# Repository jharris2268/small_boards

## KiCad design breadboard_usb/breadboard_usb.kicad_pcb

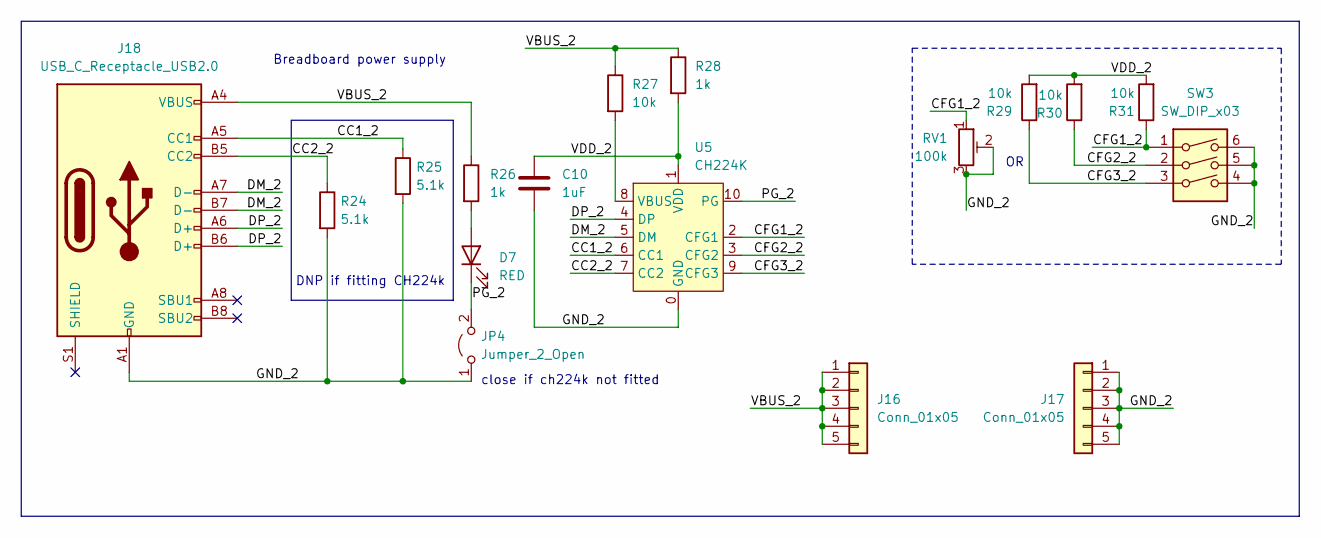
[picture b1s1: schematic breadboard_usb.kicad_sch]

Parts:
C10: 1uF; C_0805_2012Metric_Pad1.18x1.45mm_HandSolder
D7: RED; LED_0805_2012Metric_Pad1.15x1.40mm_HandSolder
J16, J17: Conn_01x05; PinHeader_1x05_P2.54mm_Vertical
J18: USB_C_Receptacle_USB2.0; usb_c_connector
JP4: Jumper_2_Open; SolderJumper-2_P1.3mm_Open_RoundedPad1.0x1.5mm
R24, R25: 5.1k; R_0805_2012Metric_Pad1.20x1.40mm_HandSolder
R26, R28: 1k; R_0805_2012Metric_Pad1.20x1.40mm_HandSolder
R27, R29, R30, R31: 10k; R_0805_2012Metric_Pad1.20x1.40mm_HandSolder
RV1: 100k; trim_pot
SW3: SW_DIP_x03; SW_DIP_SPSTx03_Slide_9.78x9.8mm_W7.62mm_P2.54mm
U5: CH224K; ESSOP-10_EP_3.9x4.9mm_P1.00mm_pth

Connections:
/CC1_2: J18.A5 (CC1), R25.1, U5.6 (CC1)
/CC2_2: J18.B5 (CC2), R24.1, U5.7 (CC2)
/CFG1_2: R31.1, RV1.1, SW3.1, U5.2 (CFG1)
/CFG2_2: R30.1, SW3.2, U5.3 (CFG2)
/CFG3_2: R29.1, SW3.3, U5.9 (CFG3)
/DM_2: J18.A7 (D-), J18.B7 (D-), U5.5 (DM)
/DP_2: J18.A6 (D+), J18.B6 (D+), U5.4 (DP)
/GND_2: C10.2, J17.1, J17.2, J17.3, J17.4, J17.5, J18.A1 (GND), J18.A12 (GND), J18.B1 (GND), J18.B12 (GND), JP4.1 (A), R24.2, R25.2, RV1.2, RV1.3, SW3.4, SW3.5, SW3.6, U5.0 (GND)
/PG_2: D7.1 (K), JP4.2 (B), U5.10 (PG)
/VBUS_2: J16.1, J16.2, J16.3, J16.4, J16.5, J18.A4 (VBUS), J18.A9 (VBUS), J18.B4 (VBUS), J18.B9 (VBUS), R26.1, R27.1, R28.1
/VDD_2: C10.1, R28.2, R29.2, R30.2, R31.2, U5.1 (VDD)
unnamed: D7.2 (A), R26.2
unnamed: R27.2, U5.8 (VBUS)

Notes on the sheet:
Breadboard power supply
DNP if fitting CH224k
close if ch224k not fitted

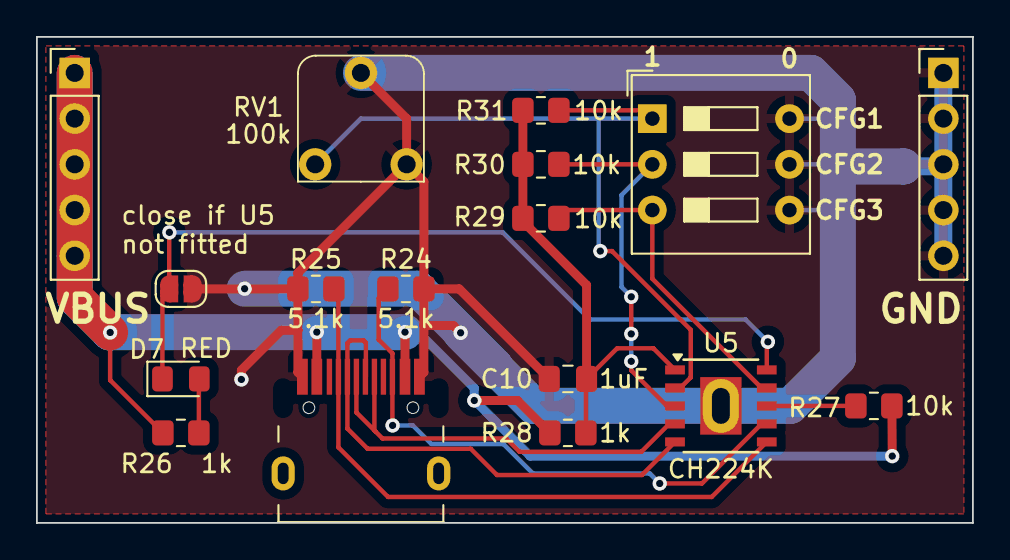
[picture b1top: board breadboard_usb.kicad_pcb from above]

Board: 2 copper layers, 52.0 x 27.0 mm, 17 parts (0 on the bottom side), 13 nets.

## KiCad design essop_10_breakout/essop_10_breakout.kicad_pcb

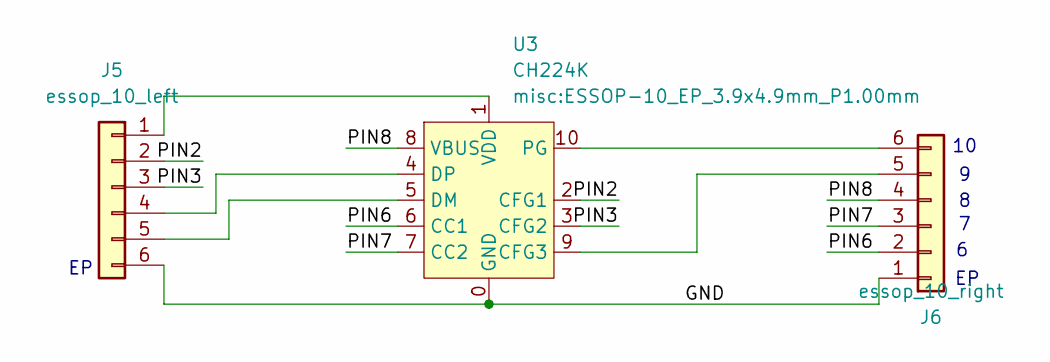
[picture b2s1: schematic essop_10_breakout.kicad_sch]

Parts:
J5: essop_10_left; PinHeader_1x06_P2.54mm_Vertical
J6: essop_10_right; PinHeader_1x06_P2.54mm_Vertical
U3: CH224K; ESSOP-10_EP_3.9x4.9mm_P1.00mm

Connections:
/GND: J5.6, J6.1, U3.0 (GND)
/PIN2: J5.2, U3.2 (CFG1)
/PIN3: J5.3, U3.3 (CFG2)
/PIN6: J6.2, U3.6 (CC1)
/PIN7: J6.3, U3.7 (CC2)
/PIN8: J6.4, U3.8 (VBUS)
unnamed: J5.1, U3.1 (VDD)
unnamed: J5.4, U3.4 (DP)
unnamed: J5.5, U3.5 (DM)
unnamed: J6.5, U3.9 (CFG3)
unnamed: J6.6, U3.10 (PG)

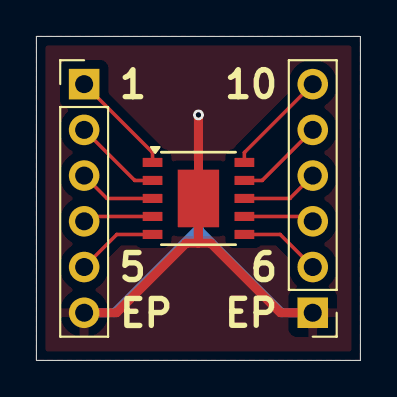
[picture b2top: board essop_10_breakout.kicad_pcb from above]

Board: 2 copper layers, 18.0 x 18.0 mm, 3 parts (0 on the bottom side), 11 nets.

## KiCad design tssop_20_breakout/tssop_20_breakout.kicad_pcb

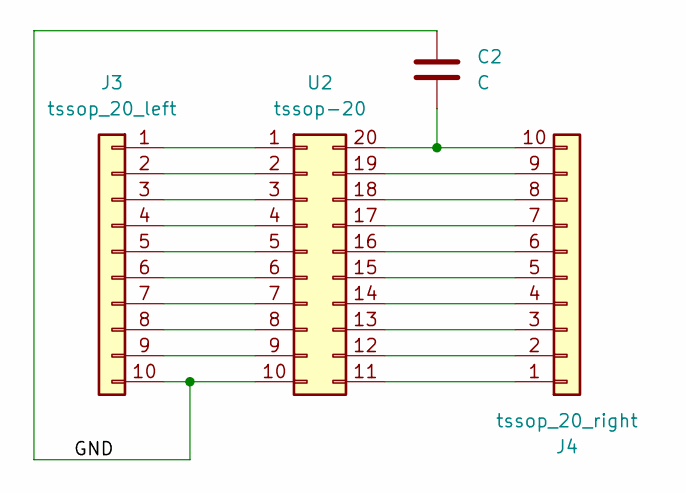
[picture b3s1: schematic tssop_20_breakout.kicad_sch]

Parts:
C2: C; C_0805_2012Metric_Pad1.18x1.45mm_HandSolder
J3: tssop_20_left; PinHeader_1x10_P2.54mm_Vertical
J4: tssop_20_right; PinHeader_1x10_P2.54mm_Vertical
U2: tssop-20; TSSOP-20_4.4x6.5mm_P0.65mm

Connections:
/GND: C2.1, J3.10, U2.10
unnamed: J3.1, U2.1
unnamed: J3.2, U2.2
unnamed: J3.3, U2.3
unnamed: J3.4, U2.4
unnamed: J3.5, U2.5
unnamed: J3.6, U2.6
unnamed: J3.7, U2.7
unnamed: J3.8, U2.8
unnamed: J3.9, U2.9
unnamed: J4.1, U2.11
unnamed: J4.2, U2.12
unnamed: J4.3, U2.13
unnamed: J4.4, U2.14
unnamed: J4.5, U2.15
unnamed: J4.6, U2.16
unnamed: J4.7, U2.17
unnamed: J4.8, U2.18
unnamed: J4.9, U2.19
unnamed: C2.2, J4.10, U2.20

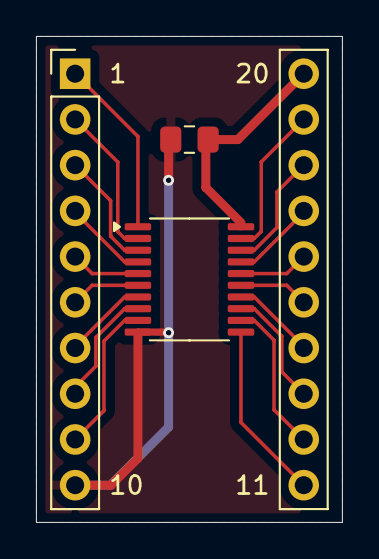
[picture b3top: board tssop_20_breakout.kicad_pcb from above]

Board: 2 copper layers, 17.0 x 27.0 mm, 4 parts (0 on the bottom side), 20 nets.
